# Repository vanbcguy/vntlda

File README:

vntlda
======

VNT LDA Controller

This software is designed to let you build yourself a VNT controller using an Arduino.  At a minimum you can run this with just a pressure sensor or just a TPS sensor plus an RPM signal, though for actual closed loop control you need all three.  The software will also work with an EGT sensor and can control a second solenoid / device - this can be used to reduce the pressure seen by the LDA when you hit high EGTs thereby reducing fuel, or it could be used to control a water/methanol injector or really do anything you might be able to think of.

Suggested Pressure Sensors
==========================

The included board design is intended to be used with Freescale MPX-series pressure sensors.  Depending on what you want to do you can use either absolute or relative / gauge pressure sensors.  Modern vehicle controls almost universally use absolute pressure sensors - this results in higher gauge pressure numbers at high altitudes providing consistent performance, however that assumes the ECU is controlling other things like fueling too.  I personally have used relative pressure sensors - they will read '0' when off boost just like a traditional boost gauge would.  This is also how wastegate turbos work.  Given that you are building your own controller I'm guessing you aren't trying to comply with strict emissions control regulations so you'll probably find the relative sensors work just fine, plus you'll probably enjoy having all the potential power your vehicle could have at lower altitudes.

Here are some example sensors:

MPX4250DP - 2 port sensor (leave the bottom port open) - max pressure 36 PSI
MPX5500DP - 2 port sensor (leave the bottom port open) - max pressure 72 PSI

Use the lowest value sensor that will meet your needs - don't be tempted to just go for the
"biggest" you can get as the larger the range of the sensor the lower its resolution. I have
used the MPX4250DP for my boost measurements and the MPX5500DP for my EMP measurements.

Suggested TPS Sensor
====================

You need "something" that will provide varying resistance as the accelerator pedal moves.  If you are using this with a Bosch VE/VP style pump there are a few options available.  Some Dodge trucks with Cummins engines and automatic transmissions have a TPS sensor mounted to the pump already - if you control the automatic transmission some other way (like a knob on the dash) then you can use the TPS for this controller.  There are also Land Rover 300 TDI pumps that came with a Bosch TPS to control their EGR system - these should bolt on to most other VE pumps as well.  If you have a 300 TDI with the EGR otherwise removed then you are already most of the way there!  If you have a different style pump then you are on your own - I recommend finding a "cheap" TPS at a parts store that you think you can work with as that way getting replacement parts will be easy.  The Land Rover TPS is frigging expensive to buy new!

Suggested RPM Sensor
====================

The project I based this off of was designed to work with a Honeywell GT101DC.  I used the factory crank position sensor on my VW AHU TDI, this required me to add an extra IC to work with magnetic reluctance sensors.  You can re-use the board design with the Honeywell sensor just by not installing a few components, namely the TI IC and its associated resistors.  Then the Honeywell wire can be connected to the appropriate hole on the board, probably.

Suggested Boost Control Solenoids
=================================

I initially used the readily avaiable GM 3-port boost control solenoids - AC Delco part number 214-474.  They seem to work fine though they are a bit noisy - take care where you mount them (ie don't screw them to the firewall as the noise will drive you nuts).  I have since moved to a VW-style "N75" valve from a Mk4 TDI; these valves are much quieter.

Logging
=======

The system can stream live data via the serial port for logging purposes.  Press the '#' key while connected via serial and the system will start streaming data in this format:

mapCorrected,vntTargetPressure,vntPositionRemapped,tpsCorrected,rpmActual,pidOutput,n75precontrol,vntMinDc,vntMaxDc,mode,targetRatioKp,targetRatioKi,targetRatioKd,boostCalculatedP,boostCalculatedI,boostCalculatedD,temp1,auxOutput,millis( / 10)

The output data can be captured with a tool like 'screen' and logged to disk. It can then be opened directly in a spreadsheet program like LibreOffice or Excel for graphing purposes.

Updates
=======

Patches and updates very welcome! The code is currently "good enough" for to get things done; many improvements could be made. Assistance reducing memory usage, implementing the missing EMP stuff, etc would be well received.

Board Notes
===========

The header for the MAX31855 amplifier board really should be flipped the other way around - I made a mistake on the board layout. This can be overcome by soldering the header and terminals to the opposite side of the MAX31855 board from normal. Everthing works fine this way.

LCD Setup
=========

This program expects to see an Adafruit RGB serial LCD backpack. It also expects the serial LCD backpack to have been configured for 115200 baud already - the display will appear corrupted if the baud rate of the LCD does not match the program rate. While I have tested successfully at 9600 baud (the Adafruit default) by far the longest running part of the program is the actual LCD update routine - while the VNT control stuff takes only a couple of ms (even with lots of float divisions!) the LCD update takes about 26-28ms at 9600 baud. It takes only 2ms at 115200 so your controller will be much happier with the faster rate. Remember it cannot calculate anything while it's writing to the LCD!

To set the baud rate on a fresh serial backpack plug it in via USB. USB doesn't make use of the baud rate so you can set it up no matter what the current settings are. Issue the following commands:

# stty -F /dev/ttyACM0 9600 -parenb cs8 -cstopb -crtscts
# echo -e "\xFE\x39\x08" > /dev/ttyACM0

The baud rate setting is stored on the LCD's EEPROM and will be briefly displayed at startup allowing you to verify the setting was saved successfully.

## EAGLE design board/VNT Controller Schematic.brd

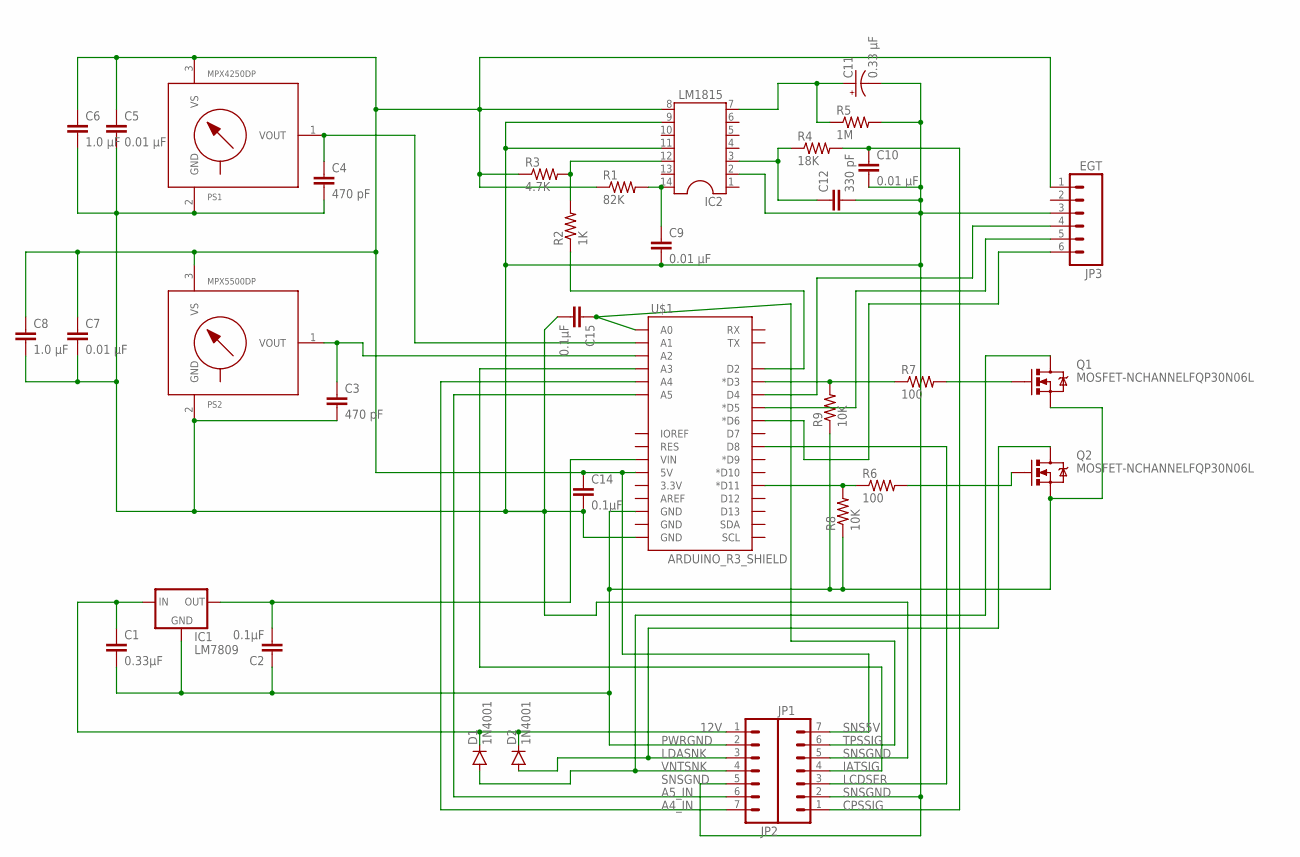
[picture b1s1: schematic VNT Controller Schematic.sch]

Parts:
C1: 0.33μF; CAP-PTH-SMALL
C2, C14, C15: 0.1μF; CAP-PTH-SMALL
C3, C4: 470 pF; CAP-PTH-SMALL
C5, C7, C9, C10: 0.01 μF; CAP-PTH-SMALL
C6, C8: 1.0 μF; CAP-PTH-SMALL
C11: 0.33 μF; CPOL-RADIAL-10UF-25V
C12: 330 pF; CAP-PTH-SMALL
D1, D2: 1N4001; DIODE-1N4001
IC1: LM7809; TO220-IGO
IC2: LM1815; SOCKET-14
JP1, JP2: M07LOCK_LONGPADS; 1X07_LOCK_LONGPADS
JP3: EGT; 1X06-SIP_LOCK
PS1: MPX4250DP; 867C-H
PS2: MPX5500DP; 867C-H
Q1, Q2: MOSFET-NCHANNELFQP30N06L; TO220V
R1: 82K; AXIAL-0.1
R2: 1K; AXIAL-0.1
R3: 4.7K; AXIAL-0.1
R4: 18K; AXIAL-0.1
R5: 1M; AXIAL-0.1
R6, R7: 100; AXIAL-0.1
R8, R9: 10K; AXIAL-0.1
U$1: ARDUINO_R3_SHIELD; UNO_R3_SHIELD

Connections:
12V: C1.1, D1.C, D2.C, IC1.IN, JP2.1
A4_IN: JP2.7, U$1.A4
A5_IN: JP2.6, U$1.A5
CPSSIG: C10.1, JP1.1, R4.P$2 (2)
IATSIG: JP1.4, U$1.A3
LCDSER: JP1.3, U$1.D8
LDASNK: D2.A, JP2.3, Q2.2 (D)
unnamed: R6.P$1 (1), R8.P$2 (2), U$1.D11 (*D11)
unnamed: C3.1, PS2.1 (VOUT), U$1.A2
unnamed: Q2.1 (G), R6.P$2 (2)
unnamed: IC2.12, R2.P$2 (2), R3.P$2 (2)
unnamed: C4.1, PS1.1 (VOUT), U$1.A1
unnamed: R2.P$1 (1), U$1.D2
unnamed: C9.1, IC2.14, R1.P$2 (2)
unnamed: R7.P$1 (1), R9.P$2 (2), U$1.D3 (*D3)
unnamed: C2.2, IC1.OUT, U$1.VIN
unnamed: Q1.1 (G), R7.P$2 (2)
unnamed: C11.1 (+), IC2.7, R5.P$1 (1)
unnamed: JP3.4, U$1.D4
unnamed: JP3.5, U$1.D5 (*D5)
unnamed: C12.1, IC2.3, R4.P$1 (1)
unnamed: JP3.6, U$1.D6 (*D6)
PWRGND: C1.2, C2.1, IC1.GND, JP2.2, Q1.3 (S), Q2.3 (S), R8.P$1 (1), R9.P$1 (1), U$1.GND@2 (GND)
SNS5V: C5.1, C6.1, C7.1, C8.1, C14.1, IC2.8, JP1.7, JP3.1, PS1.3 (VS), PS2.3 (VS), R1.P$1 (1), R3.P$1 (1), U$1.5V
SNSGND: C3.2, C4.2, C5.2, C6.2, C7.2, C8.2, C9.2, C10.2, C11.2 (-), C12.2, C14.2, C15.2, IC2.2, IC2.9, IC2.11, JP1.2, JP1.5, JP2.5, JP3.3, PS1.2 (GND), PS2.2 (GND), R5.P$2 (2), U$1.GND@0 (GND)
TPSSIG: C15.1, JP1.6, U$1.A0
VNTSNK: D1.A, JP2.4, Q1.2 (D)

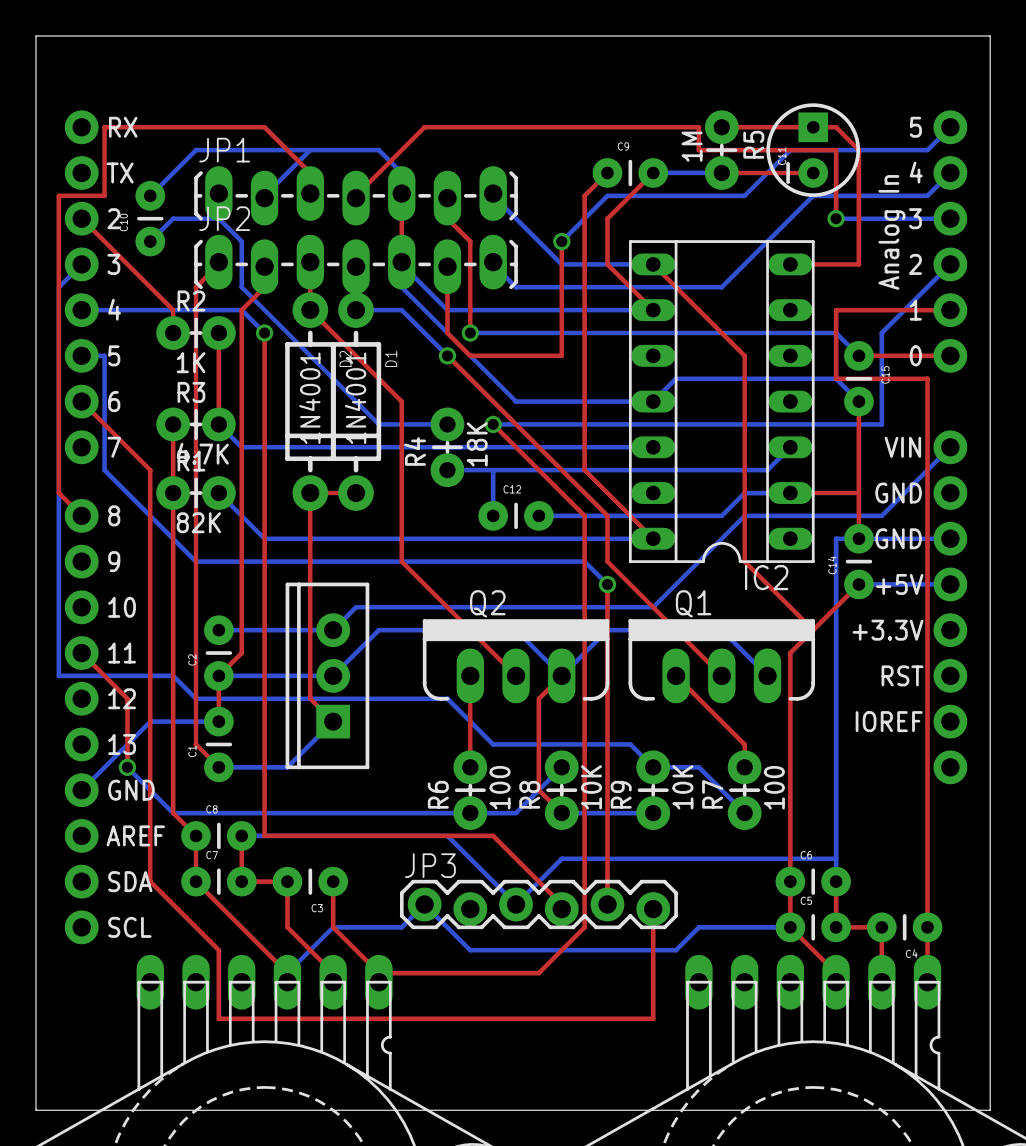
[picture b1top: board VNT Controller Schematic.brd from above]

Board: 2 copper layers, 53.0 x 59.7 mm, 35 parts (0 on the bottom side), 27 nets.

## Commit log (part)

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2014-05-14 First working version
2014-05-14 Added board design
2014-05-14 Removed original LCD code
2014-05-14 Changed datalogging to print raw values for Kp,Ki,Kd, set scaling as a constant so it can be changed in one place
2014-05-15 10x8 maps for minDC and maxDC - NOTE this build will wipe your previous settings, back them up first\!
2014-05-16 Improved all the maps to add more resolution, set Map #2 to small scale as there isn't enough RAM to hold them all
2014-05-21 Changed TPS pin settings so we will go to 0 instead of 255 if we are disconnected
2014-05-26 Added ability to export primary maps
2014-06-11 OK changed TPS pin to LOW as I had to work around a broken wire in my TPS sensor - in this mode the TPS input will float if there is no TPS connected, you may not want this
2014-06-16 On the road code change - boosted average value I think
2014-06-16 Removed some unneeded functions
2014-06-17 Removed mode select - we don't have enough memory to support dual maps. Will remove settings and second set of maps later, want to get the import/export code working first
2014-06-18 Minor comment changes
2014-06-26 Added time correction factor as our loop can compute differently - this may help stabilize things
2014-06-26 Fixed bad declaration for lastTime
2014-06-27 Messing with PID code
2014-06-27 Cleaned up double division of Ki
2014-06-27 Incorporate Kp and Kd early too for consistency - this will also help when interpreting logs
2014-06-27 Whoops - suddenly realized Kp would have been integrated the way things were done, fixed
2014-06-28 Further refinements
2014-06-28 Don't allow integral to go over 100%
2014-06-28 Take off integral 2x faster when we are over by more than PIDFineControl
2014-06-30 Cleaned up magic number for turbo saver and added a constant instead
2014-07-04 Increase delay loop plus data logging frequency
2014-07-04 Separated fine control for ramping up from double speed ramp down
2014-09-28 RPM-based integral - we have an exponential curve that we can adjust which will back off integral scaling as RPM increases, since that's how the turbo works in real life
2014-09-28 integral issue
2014-10-01 Change Ki scaling factor as values were too small in settings
2014-10-01 Fix issue where integral / derivative time factor not correctly scaled after idling
2014-10-09 Added proportional control for Kp the same as we have for Ki. Removed old coarse/fine control code that is no longer needed. Set system to open vanes fully if engine speed exceeds rpmMax as the RPM g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
2014-10-20 Altered calculation of RPM scaling plus added logging as I still do not believe it is working properly
2014-10-21 Finally working properly - minor tuning changes to add a bit more integral at higher RPM ranges.
2014-10-23 Rather than adjusting integral gain we are going to clip the integral based on RPM - that way it will stay in a reasonable range rather than keeping the value needed for low throttle at low RPM
2015-01-13 Small tuning changes
2015-01-13 Added zero RPM detection; if we don't see an RPM signal for more than 2 seconds we assume the engine is not running and set RPM to zero, otherwise it would stick at the last recorded setting.
2015-01-13 whoops helps to choose a set of maps
2015-01-14 Removed unused counter variable from main loop
2015-01-14 Separated serial reads from control loop; removed counter from datalogger page as it only executes when we do serial stuff anyhow now. Cleaned up some unused variables
2015-01-14 Added counters to measure exec time of various functions
2015-01-15 No reason to calculate RPM every loop when we aren't doing anything with the result; lets only calculate it when we are going to process the output
2015-01-15 Minor cleaning
2015-01-16 A few small speed improvements; Only set LCD color when it needs to be changed, only set up the LCD when we start up rather than rewriting everything every cycle. Also realized EGT controls had been 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
2015-01-16 Changed integral to be at 100% when at idle; we know we are going to want the vanes fully closed as soon as we step on the pedal in most circumstances
2015-01-16 Updated version string - this will clear maps and settings, be aware!
2015-01-17 Added routine to double Ki when we have overboost greater than maxPosError
2015-01-20 Minor changes to Output Tests
2015-01-20 We were rolling over our RPM calculations at higher RPMs - this one was tricky; the RPMs reported in the datalogger would be fine since they were from the past run. But when the actual datalogger ran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
2015-01-21 Better way of calculating RPM - we do a separate divide operation of all the constants ahead of time and just work with the actual variables at measuring time
2015-01-21 Realized teethSeconds would not be updated if changing number of teeth while running, RPM would have been incorrect until the next reboot. Fixed.
2015-01-25 Set integral to static value below turbo spool RPM. Once the turbo has spooled we can start integrating. This helps prevent integral windup and the resulting overshooot.
2015-01-26 minor change to avoid negative integrals; probably would never happen but let's be sure
2015-01-26 Realized I was adding to the integral and then subtracting again, whoops
2015-01-28 Tried playing with some things but going to go a different way; committing now so I can go back. If this doesn't work out, this is the point to return to!
2015-01-28 Added some comments, removed unnecessary braces
2015-01-28 Importing libraries we depend on
2015-01-28 Let's compare the actual pressure, eh?
2015-01-30 Tweaks and tuning, added status bit in datalog output
2015-01-30 Yeaaah math you do on the side of the road with your takeout in the car doesn't always work right. Some restructuring of the logic and comparisons to make this work properly as everything was bass ac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
2015-02-01 Getting too much integral on fast build leading to overshoot and oscilation. Reduce initial off-idle integral and start chopping off integral rather than just freezing it when we are in mode 5 (under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
2015-02-03 Some more tuning changes, decreased the period for the computation loop with improved results. We are going to have to speed things up I think.
2015-02-03 First draft of integer-based PID code. There's major functionality missing at this point, not sure if I would even attempt to use this yet
2015-02-04 A few fixes...
2015-02-04 I suspect the GAIN macro wasn't actually doing what it was supposed to; replaced with a function
2015-02-04 Apparently my 68ms loop time is almost entirely due to the Adafruit MAX31855 library. Also apparently it can be sped up immensely. Going to edit it, so adding it to the project.
2015-02-04 Changed to microsecond delays rather than milisecond delays for Adafruit MAX31855 library
2015-02-04 Found my error in how I was calling layoutLCD, fixed. Removed unneeded files in the project directory.
2015-02-04 Removed libraries we didn't actually need
2015-02-04 Small cleanup around initial setup routine
2015-02-05 Minor threshold tweaks
2015-02-05 Added RPM smoothing
2015-03-27 Increased EGT limits
2015-06-08 Minor tuning changes to pre spool - now transition at I=0.75
2015-06-08 Split LCD updates in two. We now alternate between the top and bottom lines to reduce the work done each cycle. Hopefully this results in 2x faster return from the LCD loop.
2015-06-08 Hopefully fixed flip flop updates to the LCD
2015-06-08 Switched to https://github.com/ControlConnection/MAX31855 library
2015-06-08 Updated so it actually works
2015-06-10 Removed rpm scale code - it was not doing anything useful
2015-06-11 We've been too aggressive with mode 5. It's slowing down responsiveness.
2015-06-11 Added logging of aux output.
2015-06-22 Removed extra semicolon
2015-07-09 Small tweaks to some settings around idle transition and slope trimming
2017-06-09 changed EGT library - now using https://github.com/engineertype/MAX31855/blob/master/MAX31855
2017-06-09 Board notes added - header for MAX31855 is backwards on the board. Oops.
2017-06-12 Including the libraries that we are using
2017-06-13 Flash the LED on the Arduino when the program is running. Add small delay on startup so the LCD has time to boot
2017-06-13 Continued cleanup; print version string to LCD on startup. Fix spelling of Average that has persisted since initial commit
2017-06-13 Tweaks to the LCD setup routine - somewhat simplified now. Write out the whole initial string rather than just filling in the static bits, that way the LCD populates all at once rather than in stages
2017-06-14 Updated copyright info and feedback email address
2017-06-15 Reimplemented idle vanes open/closed setting - it actually works now probably. No vehicle testing done yet
2017-06-15 Minor update to data logging page; it was originally set up to be used with 'meters' for displaying gauges on a laptop screen so there were some serial control characters present. We've been using it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
2017-07-20 Ignore RPM readings that don't make sense - we seem to get noise when the engine isn't running
2017-07-20 Using ResponsiveAnalogRead to filter noisy inputs. Also now correctly handling errors when reading from the MAX31855
2017-07-31 Formatting mess cleaned up. Also fixed some serious logic problems
2017-08-01 Spelling fix for derivate
2017-08-02 Cleanup of serial data logging; this hopefully will stop me from getting goofy line endings
2017-08-03 Everything is working!
2017-08-07 Updated PID routines. PID output is now actual duty cycle. Integral will now never exceed max duty cycle and will only go as high as error + integral - derivative = max duty cycle
2017-09-21 Initial attempt with n75 precontrol map. Found a few other things that should be backported if I don't stick with this; unfortunately should have split those into another commit. Oh well!
2017-09-22 Minor tweaks, removed some unused variables
2017-09-22 Updated maps based on some log data, still untested
2017-09-23 Tweak initial settings
2017-09-24 Change to P_ON_E as I'm seeing excessive pullback from PID before hitting the setpoint currently; suspect that the feed forward approach won't work with P_ON_M as it isn't aware of the changes coming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
2017-09-25 Further map refinements after data review
2017-09-26 Returned to P_ON_M for the time being; still not sure which mode I will ultimately go with
2017-09-26 Switched RPM trigger to falling rather than rising; I'm getting noise on my RPM signal. Have a feeling I flipped a couple capacitors on the board, oops. Maybe this will help?
2017-09-26 Updated maps
2017-09-27 Revised maps again...
2017-09-27 Version bump to force map reload
2017-10-07 Update libraries
2017-10-22 hookay broke stuff with the last commit and reverted; reloaded the updated maps here. Switch to P_ON_E, added no-pid RPM cut-in.
2017-10-22 Updated notes
2017-10-23 Bug fix: bad map size for mindc map. Also map updates. Will want to reduce P/I settings
2017-10-25 Removed some functions I must have duplicated without understanding; they were never being called. Changed data logging to include min/max/rpm for debugging purposes - there is an issue any time you 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
2017-10-29 Maaaaaaaaaaaaaaaaaapppssss... Updaaaaateddddddd................ Saaaaaaaaaaaaveeeeee yooooooooouuuuuuurrrrrrrr ssssssssssoooouuuuuuuulllllllllllllllgit diff vnt_lda_myPID.inogit diff vnt_lda_myPID.in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
2017-11-20 Fixed wrong variable for TPS cut-in; no sense in having PID at near-zero accelerator unless you like wound up integrals. Map updates. Significant increase to boostKp default setting as we're relying 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

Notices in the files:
parts and their libraries:
SparkFun-Boards: Licensing: Creative Commons ShareAlike 4.0 International - https://creativecommons.org/licenses/by-sa/4.0
